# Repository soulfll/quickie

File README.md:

# Quick-Key
quick key is a project for streamlining work

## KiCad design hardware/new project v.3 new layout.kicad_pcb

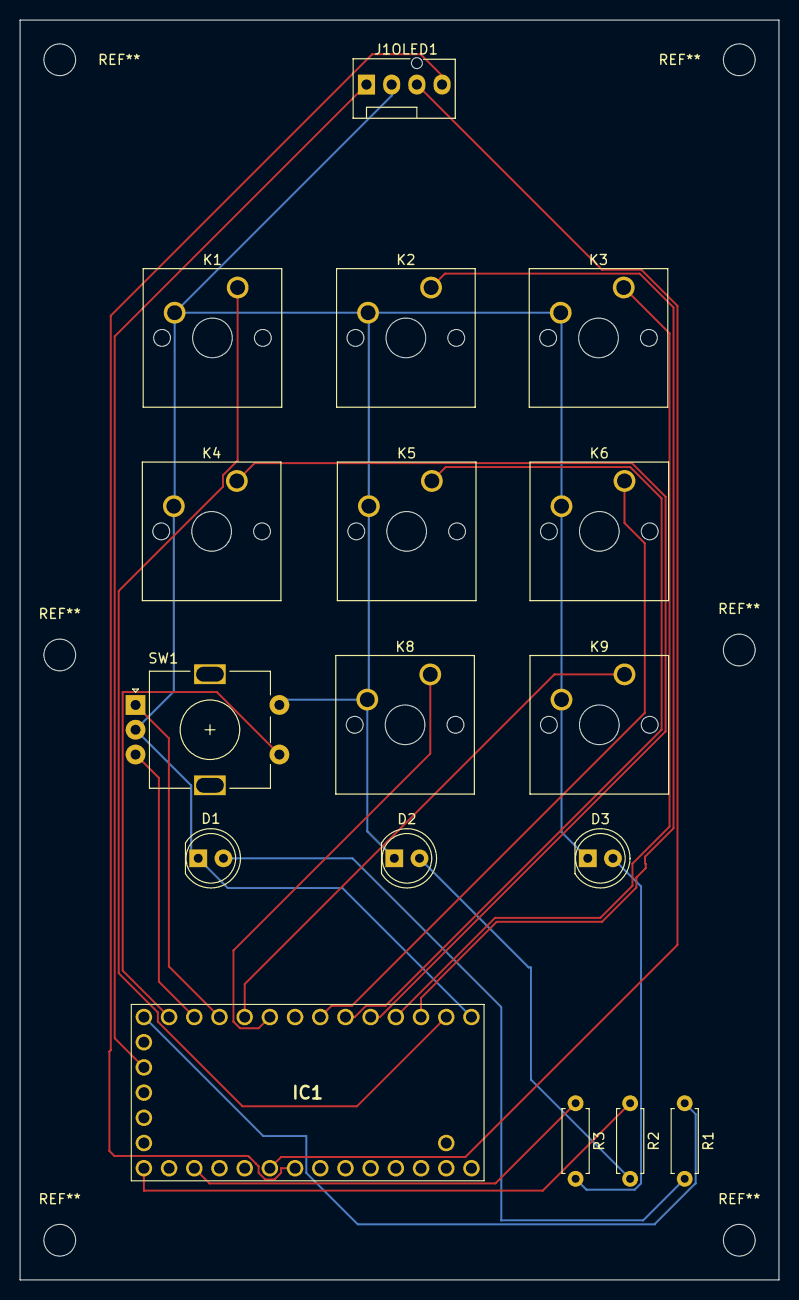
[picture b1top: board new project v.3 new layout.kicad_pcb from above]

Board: 2 copper layers, 76.5 x 127.0 mm, 17 parts (0 on the bottom side), 21 nets.

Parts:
D1, D2, D3: LED; LED_D5.0mm
IC1: TEENSY_4.0; TEENSY40
J1OLED1: Conn_01x04; FanPinHeader_1x04_P2.54mm_Vertical
K1, K2, K3, K4, K5, K6, K8, K9: SW_Push; SW_Cherry_MX_1.00u_PCB
R1, R2, R3: R; R_Axial_DIN0207_L6.3mm_D2.5mm_P7.62mm_Horizontal
SW1: RotaryEncoder_Switch; RotaryEncoder_Alps_EC11E-Switch_Vertical_H20mm

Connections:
/Teensy 10: IC1.12 (10), SW1.B
/oled scl: IC1.26 (19), J1OLED1.4
/oled sda: IC1.25 (18), J1OLED1.3
/teensy 15 red led: IC1.22 (15), R3.1
/vcc oled: IC1.16 (3.3V), J1OLED1.1
GND: D1.1 (K), D2.1 (K), D3.1 (K), IC1.1 (GND_1), J1OLED1.2, K1.2, K2.2, K3.2, K4.2, K5.2, K6.2, K8.2, K9.2, SW1.C, SW1.S2
unnamed: D1.2 (A), R1.2
unnamed: D2.2 (A), R2.2
unnamed: D3.2 (A), R3.2
unnamed: IC1.2 (0), K1.1
unnamed: IC1.3 (1), K2.1
unnamed: IC1.4 (2), K3.1
unnamed: IC1.5 (3), K4.1
unnamed: IC1.6 (4), K5.1
unnamed: IC1.7 (5), K6.1
unnamed: IC1.9 (7), K8.1
unnamed: IC1.10 (8), K9.1
unnamed: IC1.11 (9), SW1.A
unnamed: IC1.13 (11), SW1.S1
unnamed: IC1.14 (12), R1.1
unnamed: IC1.20 (13), R2.1
